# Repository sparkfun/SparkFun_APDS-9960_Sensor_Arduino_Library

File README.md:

SparkFun APDS9960 RGB and Gesture Sensor Arduino Library (non blocking fork)
=========================================================

[*Avago APDS-9960 Breakout Board (SEN-12787)*](https://www.sparkfun.com/products/12787)

This version has added apds.checkGesture() which, when repeatedly called, returns DIR_NONE most of the time but when a completed gesture is seen it returns that gesture. Updates were made with the ESP32 in mind, so the I2C uses a semaphore to prevent problems when e.g. calling apds.getProximity() from a different thread.
If this isn't required, or you're using an Arduino, the semaphore code is ifdef'd out, but that's not tested.

Getting Started
---------------

* Download the Git repository as a ZIP ("Download ZIP" button)
* Unzip
* Copy the entire library directory (APDS-9960_RGB_and_Gesture_Sensor_Arduino_Library
) to \<Arduino installation directory\>/libraries
* Open the Arduino program
* Select File -> Examples -> SparkFun_APDS9960 -> GestureTest
* Plug in your Arduino and APDS-9960 with the following connections

*-OR-*

* Use the library manager

| Arduino Pin | APDS-9960 Board | Function |
|---|---|---| 
| 3.3V | VCC | Power |
| GND | GND | Ground |
| A4 | SDA | I2C Data |
| A5 | SCL | I2C Clock |
| 2 | INT | Interrupt |

* Go to Tools -> Board and select your Arduino board
* Go to Tools -> Serial Port and select the COM port of your Arduino board
* Click "Upload"
* Go to Tools -> Serial Monitor
* Ensure the baud rate is set at 9600 baud
* Swipe your hand over the sensor in various directions!

Repository Contents
-------------------

* **/examples** - Example sketches for the library (.ino). Run these from the Arduino IDE. 
* **/src** - Source files for the library (.cpp, .h).
* **library.properties** - General library properties for the Arduino package manager. 

Documentation
--------------

* **[Installing an Arduino Library Guide](https://learn.sparkfun.com/tutorials/installing-an-arduino-library)** - Basic information on how to install an Arduino library.
* **[Product Repository](https://github.com/sparkfun/APDS-9960_RGB_and_Gesture_Sensor)** - Main repository (including hardware files) for the SparkFun_APDS9960 RGB and Gesture Sensor.
* **[Hookup Guide](https://learn.sparkfun.com/tutorials/apds-9960-rgb-and-gesture-sensor-hookup-guide)** - Basic hookup guide for the sensor.

Products that use this Library 
---------------------------------

* [SEN-12787](https://www.sparkfun.com/products/12787)- Avago APDS-9960 

Version History
---------------
* [V_1.4.1](https://github.com/sparkfun/SparkFun_APDS-9960_Sensor_Arduino_Library/tree/V_1.4.1) - Removing blank files, updating library.properties file. 
* [V_1.4.0](https://github.com/sparkfun/APDS-9960_RGB_and_Gesture_Sensor_Arduino_Library/tree/V_1.4.0) - Updated to new library structure
* V_1.3.0 - Implemented disableProximitySensor(). Thanks to jmg5150 for catching that!
* V_1.2.0 - Added pinMode line to GestureTest demo to fix interrupt bug with some Arduinos
* V_1.1.0 - Updated GestureTest demo to not freeze with fast swipes
* V_1.0.0: Initial release
* Ambient and RGB light sensing implemented
* Ambient light interrupts working
* Proximity sensing implemented
* Proximity interrupts working
* Gesture (UP, DOWN, LEFT, RIGHT, NEAR, FAR) sensing implemented

License Information
-------------------

This product is _**open source**_! 

The **code** is beerware; if you see me (or any other SparkFun employee) at the local, and you've found our code helpful, please buy us a round!

Please use, reuse, and modify these files as you see fit. Please maintain attribution to SparkFun Electronics and release anything derivative under the same license.

Distributed as-is; no warranty is given.

- Your friends at SparkFun.

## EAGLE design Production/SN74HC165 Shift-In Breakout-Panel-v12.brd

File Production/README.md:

These are the production files SparkFun uses for printing PCBs, as well as the Eagle files for our test beds.

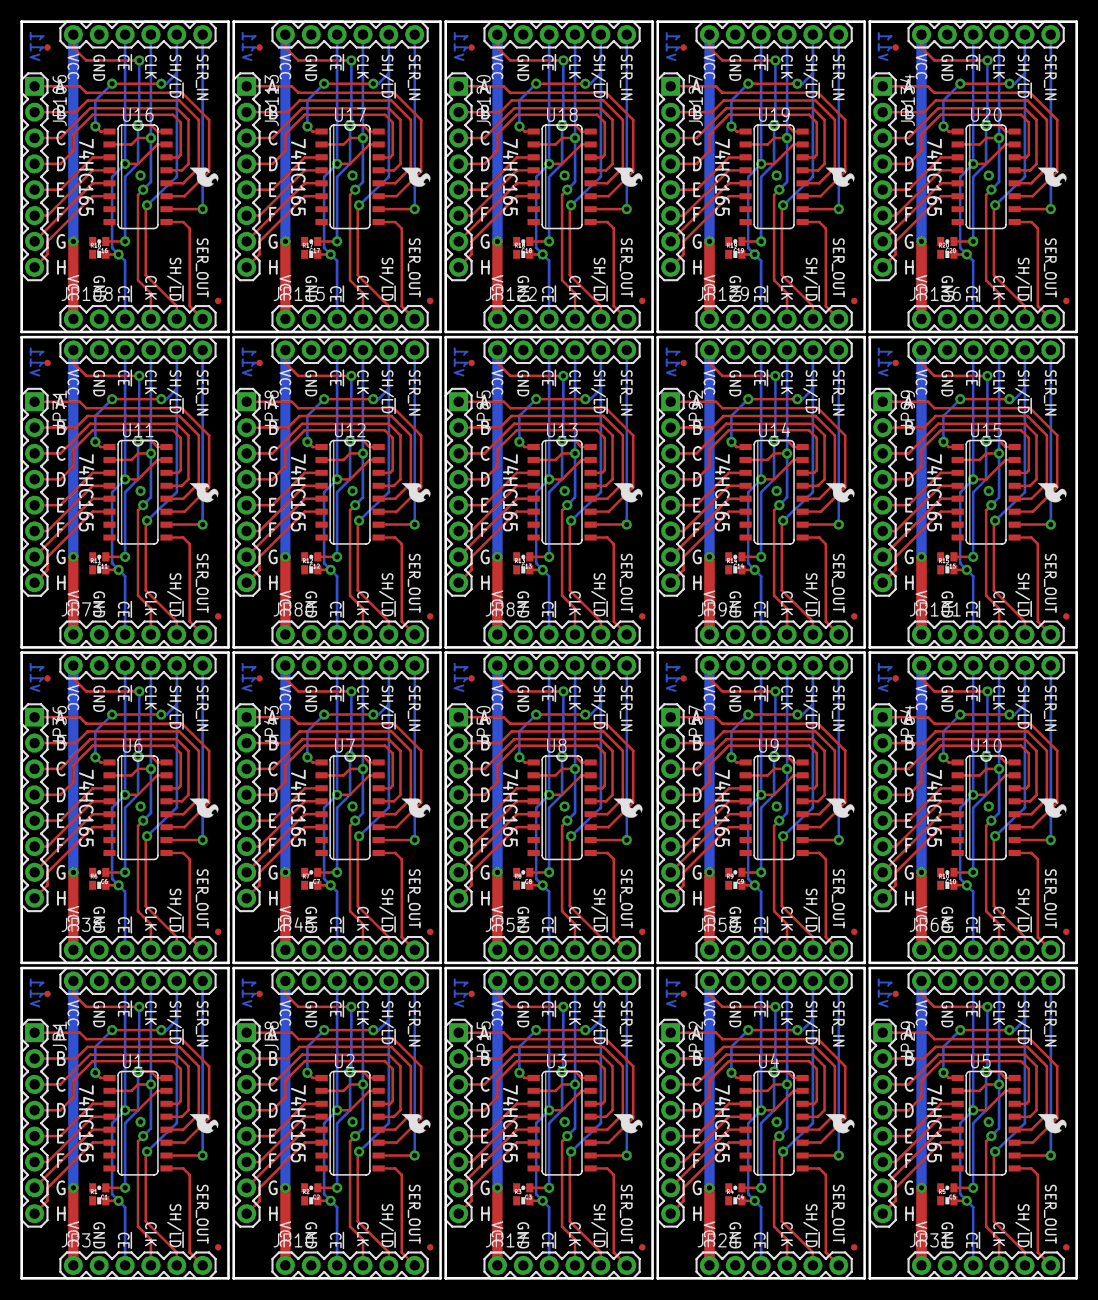
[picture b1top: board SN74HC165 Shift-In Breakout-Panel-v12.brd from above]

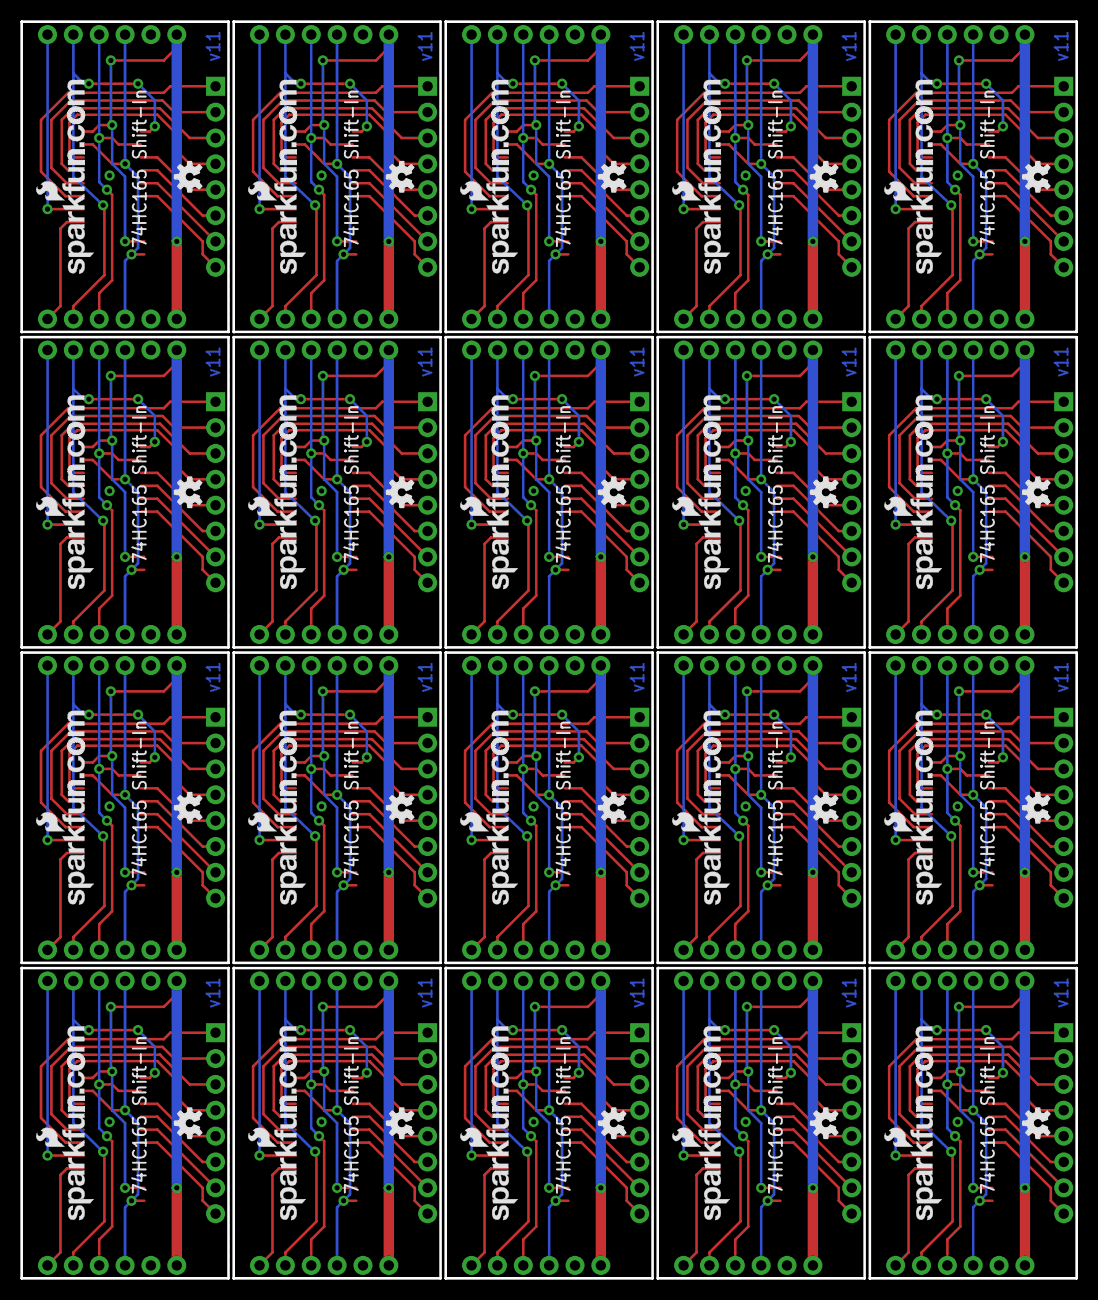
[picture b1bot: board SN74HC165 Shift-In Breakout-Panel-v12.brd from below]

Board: 2 copper layers, 103.6 x 123.4 mm, 220 parts (40 on the bottom side), 300 nets.

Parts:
C1, C2, C3, C4, C5, C6, C7, C8, C9, C10, C11, C12, C13, C14, C15, C16, C17, C18, C19, C20: .1uF; 0402-CAP
JP1, JP8, JP15, JP22, JP29, JP36, JP43, JP50, JP57, JP64, JP71, JP78, JP85, JP92, JP99, JP106, JP113, JP120, JP127, JP134: 1X08
JP2, JP3, JP9, JP10, JP16, JP17, JP23, JP24, JP30, JP31, JP37, JP38, JP44, JP45, JP51, JP52, JP58, JP59, JP65, JP66, JP72, JP73, JP79, JP80, JP86, JP87, JP93, JP94, JP100, JP101, JP107, JP108, JP114, JP115, JP121, JP122, JP128, JP129, JP135, JP136: 1X06
JP4, JP11, JP18, JP25, JP32, JP39, JP46, JP53, JP60, JP67, JP74, JP81, JP88, JP95, JP102, JP109, JP116, JP123, JP130, JP137: LOGO-SFESK; SFE-LOGO-FLAME
JP5, JP12, JP19, JP26, JP33, JP40, JP47, JP54, JP61, JP68, JP75, JP82, JP89, JP96, JP103, JP110, JP117, JP124, JP131, JP138: LOGO-SFENEW; SFE-NEW-WEBLOGO
JP6, JP7, JP13, JP14, JP20, JP21, JP27, JP28, JP34, JP35, JP41, JP42, JP48, JP49, JP55, JP56, JP62, JP63, JP69, JP70, JP76, JP77, JP83, JP84, JP90, JP91, JP97, JP98, JP104, JP105, JP111, JP112, JP118, JP119, JP125, JP126, JP132, JP133, JP139, JP140: FIDUCIALUFIDUCIAL; MICRO-FIDUCIAL
R1, R2, R3, R4, R5, R6, R7, R8, R9, R10, R11, R12, R13, R14, R15, R16, R17, R18, R19, R20: 10k; 0402-RES
U1, U2, U3, U4, U5, U6, U7, U8, U9, U10, U11, U12, U13, U14, U15, U16, U17, U18, U19, U20: 74HC165D; SO16
U$1, U$2, U$3, U$4, U$5, U$6, U$7, U$8, U$9, U$10, U$11, U$12, U$13, U$14, U$15, U$16, U$17, U$18, U$19, U$20: OSHW-LOGOS; OSHW-LOGO-S

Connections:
!CLK_ENABLE: JP2.3, JP3.3, R1.2, U1.15
!CLK_ENABLE1: JP9.3, JP10.3, R2.2, U2.15
!CLK_ENABLE2: JP16.3, JP17.3, R3.2, U3.15
!CLK_ENABLE3: JP23.3, JP24.3, R4.2, U4.15
!CLK_ENABLE4: JP30.3, JP31.3, R5.2, U5.15
!CLK_ENABLE5: JP37.3, JP38.3, R6.2, U6.15
!CLK_ENABLE6: JP44.3, JP45.3, R7.2, U7.15
!CLK_ENABLE7: JP51.3, JP52.3, R8.2, U8.15
!CLK_ENABLE8: JP58.3, JP59.3, R9.2, U9.15
!CLK_ENABLE9: JP65.3, JP66.3, R10.2, U10.15
!CLK_ENABLE10: JP72.3, JP73.3, R11.2, U11.15
!CLK_ENABLE11: JP79.3, JP80.3, R12.2, U12.15
!CLK_ENABLE12: JP86.3, JP87.3, R13.2, U13.15
!CLK_ENABLE13: JP93.3, JP94.3, R14.2, U14.15
!CLK_ENABLE14: JP100.3, JP101.3, R15.2, U15.15
!CLK_ENABLE15: JP107.3, JP108.3, R16.2, U16.15
!CLK_ENABLE16: JP114.3, JP115.3, R17.2, U17.15
!CLK_ENABLE17: JP121.3, JP122.3, R18.2, U18.15
!CLK_ENABLE18: JP128.3, JP129.3, R19.2, U19.15
!CLK_ENABLE19: JP135.3, JP136.3, R20.2, U20.15
A: JP1.1, U1.11
A1: JP8.1, U2.11
A2: JP15.1, U3.11
A3: JP22.1, U4.11
A4: JP29.1, U5.11
A5: JP36.1, U6.11
A6: JP43.1, U7.11
A7: JP50.1, U8.11
A8: JP57.1, U9.11
A9: JP64.1, U10.11
A10: JP71.1, U11.11
A11: JP78.1, U12.11
A12: JP85.1, U13.11
A13: JP92.1, U14.11
A14: JP99.1, U15.11
A15: JP106.1, U16.11
A16: JP113.1, U17.11
A17: JP120.1, U18.11
A18: JP127.1, U19.11
A19: JP134.1, U20.11
B: JP1.2, U1.12
B1: JP8.2, U2.12
B2: JP15.2, U3.12
B3: JP22.2, U4.12
B4: JP29.2, U5.12
B5: JP36.2, U6.12
B6: JP43.2, U7.12
B7: JP50.2, U8.12
B8: JP57.2, U9.12
B9: JP64.2, U10.12
B10: JP71.2, U11.12
B11: JP78.2, U12.12
B12: JP85.2, U13.12
B13: JP92.2, U14.12
B14: JP99.2, U15.12
B15: JP106.2, U16.12
B16: JP113.2, U17.12
B17: JP120.2, U18.12
B18: JP127.2, U19.12
B19: JP134.2, U20.12
C: JP1.3, U1.13
C1: JP8.3, U2.13
C2: JP15.3, U3.13
C3: JP22.3, U4.13
C4: JP29.3, U5.13
C5: JP36.3, U6.13
C6: JP43.3, U7.13
C7: JP50.3, U8.13
C8: JP57.3, U9.13
C9: JP64.3, U10.13
C10: JP71.3, U11.13
C11: JP78.3, U12.13
C12: JP85.3, U13.13
C13: JP92.3, U14.13
C14: JP99.3, U15.13
C15: JP106.3, U16.13
C16: JP113.3, U17.13
C17: JP120.3, U18.13
C18: JP127.3, U19.13
C19: JP134.3, U20.13
CLK: JP2.4, JP3.4, U1.2
CLK1: JP9.4, JP10.4, U2.2
CLK2: JP16.4, JP17.4, U3.2
CLK3: JP23.4, JP24.4, U4.2
CLK4: JP30.4, JP31.4, U5.2
CLK5: JP37.4, JP38.4, U6.2
CLK6: JP44.4, JP45.4, U7.2
CLK7: JP51.4, JP52.4, U8.2
CLK8: JP58.4, JP59.4, U9.2
CLK9: JP65.4, JP66.4, U10.2
CLK10: JP72.4, JP73.4, U11.2
CLK11: JP79.4, JP80.4, U12.2
CLK12: JP86.4, JP87.4, U13.2
CLK13: JP93.4, JP94.4, U14.2
CLK14: JP100.4, JP101.4, U15.2
CLK15: JP107.4, JP108.4, U16.2
CLK16: JP114.4, JP115.4, U17.2
CLK17: JP121.4, JP122.4, U18.2
CLK18: JP128.4, JP129.4, U19.2
CLK19: JP135.4, JP136.4, U20.2
D: JP1.4, U1.14
D1: JP8.4, U2.14
D2: JP15.4, U3.14
D3: JP22.4, U4.14
D4: JP29.4, U5.14
D5: JP36.4, U6.14
D6: JP43.4, U7.14
D7: JP50.4, U8.14
D8: JP57.4, U9.14
D9: JP64.4, U10.14
D10: JP71.4, U11.14
D11: JP78.4, U12.14
D12: JP85.4, U13.14
D13: JP92.4, U14.14
D14: JP99.4, U15.14
D15: JP106.4, U16.14
D16: JP113.4, U17.14
D17: JP120.4, U18.14
D18: JP127.4, U19.14
D19: JP134.4, U20.14
E: JP1.5, U1.3
E1: JP8.5, U2.3
E2: JP15.5, U3.3
E3: JP22.5, U4.3
E4: JP29.5, U5.3
E5: JP36.5, U6.3
E6: JP43.5, U7.3
E7: JP50.5, U8.3
E8: JP57.5, U9.3
E9: JP64.5, U10.3
E10: JP71.5, U11.3
E11: JP78.5, U12.3
E12: JP85.5, U13.3
E13: JP92.5, U14.3
E14: JP99.5, U15.3
E15: JP106.5, U16.3
E16: JP113.5, U17.3
E17: JP120.5, U18.3
E18: JP127.5, U19.3
E19: JP134.5, U20.3
F: JP1.6, U1.4
F1: JP8.6, U2.4
F2: JP15.6, U3.4
F3: JP22.6, U4.4
F4: JP29.6, U5.4
F5: JP36.6, U6.4
F6: JP43.6, U7.4
F7: JP50.6, U8.4
F8: JP57.6, U9.4
F9: JP64.6, U10.4
F10: JP71.6, U11.4
F11: JP78.6, U12.4
F12: JP85.6, U13.4
F13: JP92.6, U14.4
F14: JP99.6, U15.4
F15: JP106.6, U16.4
F16: JP113.6, U17.4
F17: JP120.6, U18.4
F18: JP127.6, U19.4
F19: JP134.6, U20.4
G: JP1.7, U1.5
G1: JP8.7, U2.5
G2: JP15.7, U3.5
G3: JP22.7, U4.5
G4: JP29.7, U5.5
G5: JP36.7, U6.5
G6: JP43.7, U7.5
G7: JP50.7, U8.5
G8: JP57.7, U9.5
G9: JP64.7, U10.5
G10: JP71.7, U11.5
G11: JP78.7, U12.5
G12: JP85.7, U13.5
G13: JP92.7, U14.5
G14: JP99.7, U15.5
G15: JP106.7, U16.5
G16: JP113.7, U17.5
G17: JP120.7, U18.5
G18: JP127.7, U19.5
G19: JP134.7, U20.5
GND: C1.2, JP2.2, JP3.2, R1.1, U1.8
GND1: C2.2, JP9.2, JP10.2, R2.1, U2.8
GND2: C3.2, JP16.2, JP17.2, R3.1, U3.8
GND3: C4.2, JP23.2, JP24.2, R4.1, U4.8
GND4: C5.2, JP30.2, JP31.2, R5.1, U5.8
GND5: C6.2, JP37.2, JP38.2, R6.1, U6.8
GND6: C7.2, JP44.2, JP45.2, R7.1, U7.8
GND7: C8.2, JP51.2, JP52.2, R8.1, U8.8
GND8: C9.2, JP58.2, JP59.2, R9.1, U9.8
GND9: C10.2, JP65.2, JP66.2, R10.1, U10.8
GND10: C11.2, JP72.2, JP73.2, R11.1, U11.8
GND11: C12.2, JP79.2, JP80.2, R12.1, U12.8
GND12: C13.2, JP86.2, JP87.2, R13.1, U13.8
GND13: C14.2, JP93.2, JP94.2, R14.1, U14.8
GND14: C15.2, JP100.2, JP101.2, R15.1, U15.8
GND15: C16.2, JP107.2, JP108.2, R16.1, U16.8
GND16: C17.2, JP114.2, JP115.2, R17.1, U17.8
GND17: C18.2, JP121.2, JP122.2, R18.1, U18.8
GND18: C19.2, JP128.2, JP129.2, R19.1, U19.8
GND19: C20.2, JP135.2, JP136.2, R20.1, U20.8
H: JP1.8, U1.6
H1: JP8.8, U2.6
H2: JP15.8, U3.6
H3: JP22.8, U4.6
H4: JP29.8, U5.6
H5: JP36.8, U6.6
H6: JP43.8, U7.6
H7: JP50.8, U8.6
H8: JP57.8, U9.6
H9: JP64.8, U10.6
H10: JP71.8, U11.6
H11: JP78.8, U12.6
H12: JP85.8, U13.6
H13: JP92.8, U14.6
H14: JP99.8, U15.6
H15: JP106.8, U16.6
H16: JP113.8, U17.6
H17: JP120.8, U18.6
H18: JP127.8, U19.6
H19: JP134.8, U20.6
SERIAL_IN: JP2.6, U1.10
SERIAL_IN1: JP9.6, U2.10
SERIAL_IN2: JP16.6, U3.10
SERIAL_IN3: JP23.6, U4.10
SERIAL_IN4: JP30.6, U5.10
SERIAL_IN5: JP37.6, U6.10
SERIAL_IN6: JP44.6, U7.10
SERIAL_IN7: JP51.6, U8.10
SERIAL_IN8: JP58.6, U9.10
SERIAL_IN9: JP65.6, U10.10
SERIAL_IN10: JP72.6, U11.10
SERIAL_IN11: JP79.6, U12.10
SERIAL_IN12: JP86.6, U13.10
SERIAL_IN13: JP93.6, U14.10
SERIAL_IN14: JP100.6, U15.10
SERIAL_IN15: JP107.6, U16.10
SERIAL_IN16: JP114.6, U17.10
SERIAL_IN17: JP121.6, U18.10
SERIAL_IN18: JP128.6, U19.10
SERIAL_IN19: JP135.6, U20.10
SERIAL_OUT: JP3.6, U1.9
SERIAL_OUT1: JP10.6, U2.9
SERIAL_OUT2: JP17.6, U3.9
SERIAL_OUT3: JP24.6, U4.9
SERIAL_OUT4: JP31.6, U5.9
SERIAL_OUT5: JP38.6, U6.9
SERIAL_OUT6: JP45.6, U7.9
SERIAL_OUT7: JP52.6, U8.9
SERIAL_OUT8: JP59.6, U9.9
SERIAL_OUT9: JP66.6, U10.9
SERIAL_OUT10: JP73.6, U11.9
SERIAL_OUT11: JP80.6, U12.9
SERIAL_OUT12: JP87.6, U13.9
SERIAL_OUT13: JP94.6, U14.9
SERIAL_OUT14: JP101.6, U15.9
SERIAL_OUT15: JP108.6, U16.9
SERIAL_OUT16: JP115.6, U17.9
SERIAL_OUT17: JP122.6, U18.9
SERIAL_OUT18: JP129.6, U19.9
SERIAL_OUT19: JP136.6, U20.9
SHIFT/!LOAD: JP2.5, JP3.5, U1.1
SHIFT/!LOAD1: JP9.5, JP10.5, U2.1
SHIFT/!LOAD2: JP16.5, JP17.5, U3.1
SHIFT/!LOAD3: JP23.5, JP24.5, U4.1
SHIFT/!LOAD4: JP30.5, JP31.5, U5.1
SHIFT/!LOAD5: JP37.5, JP38.5, U6.1
SHIFT/!LOAD6: JP44.5, JP45.5, U7.1
SHIFT/!LOAD7: JP51.5, JP52.5, U8.1
SHIFT/!LOAD8: JP58.5, JP59.5, U9.1
SHIFT/!LOAD9: JP65.5, JP66.5, U10.1
SHIFT/!LOAD10: JP72.5, JP73.5, U11.1
SHIFT/!LOAD11: JP79.5, JP80.5, U12.1
SHIFT/!LOAD12: JP86.5, JP87.5, U13.1
SHIFT/!LOAD13: JP93.5, JP94.5, U14.1
SHIFT/!LOAD14: JP100.5, JP101.5, U15.1
SHIFT/!LOAD15: JP107.5, JP108.5, U16.1
SHIFT/!LOAD16: JP114.5, JP115.5, U17.1
SHIFT/!LOAD17: JP121.5, JP122.5, U18.1
SHIFT/!LOAD18: JP128.5, JP129.5, U19.1
SHIFT/!LOAD19: JP135.5, JP136.5, U20.1
VCC: C1.1, JP2.1, JP3.1, U1.16
VCC1: C2.1, JP9.1, JP10.1, U2.16
VCC2: C3.1, JP16.1, JP17.1, U3.16
VCC3: C4.1, JP23.1, JP24.1, U4.16
VCC4: C5.1, JP30.1, JP31.1, U5.16
VCC5: C6.1, JP37.1, JP38.1, U6.16
VCC6: C7.1, JP44.1, JP45.1, U7.16
VCC7: C8.1, JP51.1, JP52.1, U8.16
VCC8: C9.1, JP58.1, JP59.1, U9.16
VCC9: C10.1, JP65.1, JP66.1, U10.16
VCC10: C11.1, JP72.1, JP73.1, U11.16
VCC11: C12.1, JP79.1, JP80.1, U12.16
VCC12: C13.1, JP86.1, JP87.1, U13.16
VCC13: C14.1, JP93.1, JP94.1, U14.16
VCC14: C15.1, JP100.1, JP101.1, U15.16
VCC15: C16.1, JP107.1, JP108.1, U16.16
VCC16: C17.1, JP114.1, JP115.1, U17.16
VCC17: C18.1, JP121.1, JP122.1, U18.16
VCC18: C19.1, JP128.1, JP129.1, U19.16
VCC19: C20.1, JP135.1, JP136.1, U20.16

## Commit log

2013-04-16 Creating a proper repo structure
2013-04-16 remove extraneous font
2013-04-16 Fix format issues
2013-04-17 Added example files
2013-04-17 add all the files in all the folders
2013-04-17 Add README files to each sub folder.
2013-04-17 Fix the .gitignore and .gitattributes files
2013-04-17 Add Fritzing source files & update README
2013-09-26 Add a few SF useful items to .gitignore
2013-12-18 Test Commit
    Adding an additional line to the read me
2013-12-18 Update README.md
    Deleted the line just added
2014-02-04 Updating CC 4.0 license and adding standard header template
2015-02-16 Removed excessive line
2015-02-26 Changing Fritzing part information
2015-03-03 Updating README formatting
2015-03-31 Updating directories for fritzing and 3D models
2015-04-06 Test for commit messages
    fixing issue #2
2015-04-21 Removed white space from file name
2015-04-22 Swapping format to Arduino library compatibility
2015-04-22 Repo cleanup for ARduino library compatibility
2015-04-23 Fixing structure more to be compliant with Arduino library requirements
2015-04-23 Updating README with Arduino library specific documentation
2015-04-23 Fixing formatting
2015-04-26 Restructured
2015-04-29 Part of the new arduino lib format updates
2015-05-13 Removing unnecessary files, updating library properties
2015-05-13 Adding version number to README
2015-07-21 Updating library name
2016-05-10 @PlatformIO Library Registry manifest file
2016-11-21 Modify for compatibility with ESP8266
    Change pins, wire.begin with pins as parameters since esp8266 doesn’t
    have hw I2c
2017-07-10 Improve README.md
    - Split "Getting Started" section into "Library Installation" and "Getting Started". This fixes the previous awkwardness of the two installation options breaking the flow to opening the example.
    - Manual installation to sketchbook folder, not to the IDE installation folder. Installing to the IDE installation folder is a bad idea because the library will need to be reinstalled whenever the ID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
    - Link to SparkFun's instructions for Library Manager installation.
    - Use correct menu path to example. The Arduino IDE uses the name value set in library.properties.
    - Trim trailing whitespace.
    - Fix menu path to Port menu.
2020-05-05 Allow reading status register
    Allow reading the status register. This register is important in determining if the value of the ALS and proximity sensor is valid.
    Not changing the read funcionts since I assume there was a reason that the status register was not checked (performance?).
2020-05-05 Add getStatusRegister to header
2020-05-07 Update library.properties
    Bump version
2021-06-15 Updated to add non-blocking usage on the ESP32.
2021-06-15 ifdef out the semaphore if it's not ESP32 we're targeting
2021-06-15 Added example program for non-blocking gesture reading
2022-10-26 attachInterpt to pin actually being used for INT
2023-09-17 [FEATURE] Support a clone with different device id
    Add support for a clone of the APDS9960 with a different device
    id (0xA8) which otherwise cannot be initialized.
2024-03-13 Added cheap chinese clone ID as valid device

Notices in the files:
parts and their libraries:
SparkFun-Aesthetics: Licensing: CC v3.0 Share-Alike You are welcome to use this library for commercial purposes.
